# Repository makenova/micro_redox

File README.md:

# micro_redox

A family of 40% choc keyboards(34 keys) inspired by the Microdox and Ferris keyboards. 

 - The **micro_redox_split** is a pro-micro powered reversible split that does not require diodes.
 - The **micro_redox_semi_spit** is an integrated mcu semi split with usb-c and a rotary encoder.

Both boards can use either hot-swap sockets or the switches can be soldered directly to the pcb.

## Inspiration and differences

The Microdox(36 key MX spaced split) from Boardsource is a great keyboard. It was my first choc board, and after trying out a few keymaps, I realized I didn't need the outer thumb keys. In my experience, those keys are difficult to reach and do not serve a purpose on the keymap I've settled on.   
The Ferris(34 key choc spaced split) is another great keyboard. I like the look of the Ferris but a couple things made it uncomfortable for me to use:

* the thumb cluster is too close to the alphas 
* the pinky stagger is aggressive 

For the micro_redox family, I have kept the column stagger from the Microdox, made it choc spaced, and removed the outter thumb keys. I have also kept the distance between the homing keys and the thumb keys because I find it comfortable. Finally, I rotated the innermost thumb key which means that only 1u keycaps will fit there.  
For the split, I've also used a reversible pro-micro footprint so that both of them can face the same way i.e. component side down. It's a cleaner look.

## Libraries

These libraries that help me move fast. I may not actually be using them in this project, but adding them to keyboard projects is a habit. The are all added as git submodules so make sure you pull them down after you pull the repo.  
My thanks to the authors for sharing.

- [Keebio-components](https://github.com/keebio/keebio-components)
  - [@keebio](https://github.com/keebio)
- [Keebio-parts.pretty](https://github.com/keebio/Keebio-Parts.pretty)
  - [@keebio](https://github.com/keebio)
- [keyswtiches.pretty](https://github.com/daprice/keyswitches.pretty)
  - [@daprice](https://github.com/daprice)
- [random-keyboard-parts.pretty](https://github.com/ai03-2725/random-keyboard-parts.pretty)
  - [@ai03-2725](https://github.com/ai03-2725)
- [https://github.com/foostan/kbd](https://github.com/foostan/kbd)
  - [@foostan](https://github.com/foostan)
- [Customizable Rotary Encoder Knob](https://www.thingiverse.com/thing:2797118)
  - [tsw](https://www.thingiverse.com/tsw/designs)

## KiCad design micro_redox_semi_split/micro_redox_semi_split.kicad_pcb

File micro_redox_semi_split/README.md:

# micro_redox_semi_split

### Features

- USB C
- integrated mcu
- rotary encoder
- choc spaced
- hot-swap or soldered

There are production files in the "gerbers" directory for the pcb and a skeleton case.
Simply upload the zip files to your PCB manufacturer of choice.

If you do not get this assembled by a factory you can find an interactive BOM in `bom` directory.

Starting firmware can be found on my QMK fork in the [`makenova`](https://github.com/makenova/qmk_firmware/tree/makenova/keyboards/makenova//micro_redox/semi_split) branch.

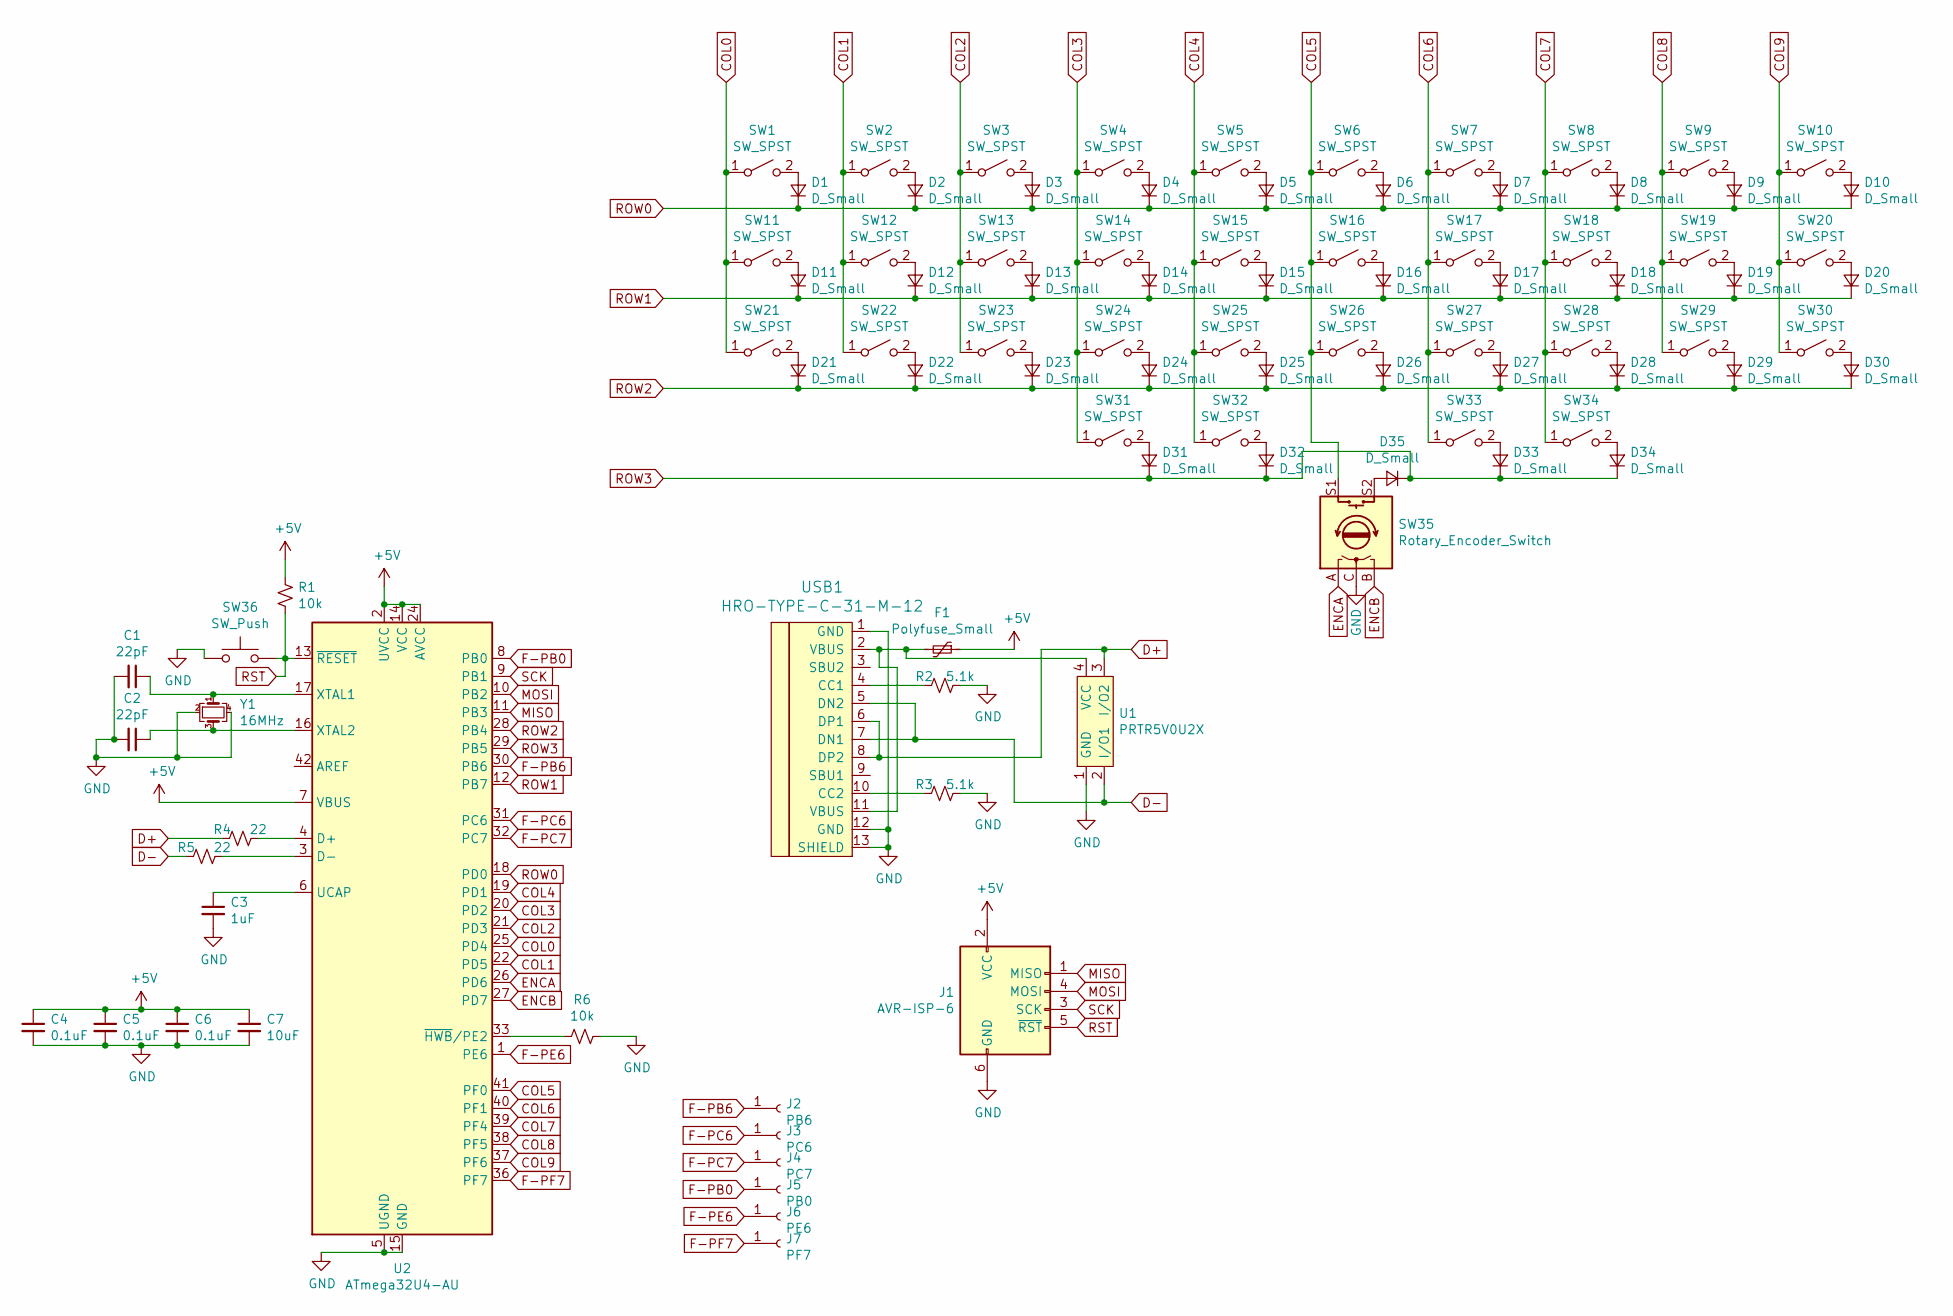
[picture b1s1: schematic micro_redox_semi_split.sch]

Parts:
C1, C2: 22pF; C_0805_2012Metric_Pad1.15x1.40mm_HandSolder
C3: 1uF; C_0805_2012Metric_Pad1.15x1.40mm_HandSolder
C4, C5, C6: 0.1uF; C_0805_2012Metric_Pad1.15x1.40mm_HandSolder
C7: 10uF; C_0805_2012Metric_Pad1.15x1.40mm_HandSolder
D1, D2, D3, D4, D5, D6, D7, D8, D9, D10, D11, D12, D13, D14, D15, D16, D17, D18, D19, D20, D21, D22, D23, D24, D25, D26, D27, D28, D29, D30, D31, D32, D33, D34, D35: D_Small; D_SOD-123
F1: Polyfuse_Small; Fuse_1206_3216Metric_Pad1.42x1.75mm_HandSolder
J1: AVR-ISP-6; ICSP-Header-ZigZag
J2: PB6; SinglePad
J3: PC6; SinglePad
J4: PC7; SinglePad
J5: PB0; SinglePad
J6: PE6; SinglePad
J7: PF7; SinglePad
R1, R6: 10k; R_0805_2012Metric_Pad1.15x1.40mm_HandSolder
R2, R3: 5.1k; R_0805_2012Metric_Pad1.15x1.40mm_HandSolder
R4, R5: 22; R_0805_2012Metric_Pad1.15x1.40mm_HandSolder
SW1, SW2, SW3, SW4, SW5, SW6, SW7, SW8, SW9, SW10, SW11, SW12, SW13, SW14, SW15, SW16, SW17, SW18, SW19, SW20, SW21, SW22, SW23, SW24, SW25, SW26, SW27, SW28, SW29, SW30, SW31, SW32, SW33, SW34: SW_SPST; Kailh_socket_PG1350_optional
SW35: Rotary_Encoder_Switch; RotaryEncoder_Alps_EC11E-Switch_Vertical_H20mm
SW36: SW_Push; SW_SPST_TL3342
U1: PRTR5V0U2X; SOT-143B
U2: ATmega32U4-AU; TQFP-44_10x10mm_P0.8mm
USB1: HRO-TYPE-C-31-M-12; HRO-TYPE-C-31-M-12-Assembly
Y1: 16MHz; Crystal_SMD_3225-4Pin_3.2x2.5mm_HandSoldering

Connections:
+5V: C4.1, C5.1, C6.1, C7.1, F1.1, J1.2 (VCC), R1.2, U2.2 (UVCC), U2.7 (VBUS), U2.14 (VCC), U2.24 (AVCC), U2.34 (VCC), U2.44 (AVCC)
COL0: SW1.1 (A), SW11.1 (A), SW21.1 (A), U2.25 (PD4)
COL1: SW2.1 (A), SW12.1 (A), SW22.1 (A), U2.22 (PD5)
COL2: SW3.1 (A), SW13.1 (A), SW23.1 (A), U2.21 (PD3)
COL3: SW4.1 (A), SW14.1 (A), SW24.1 (A), SW31.1 (A), U2.20 (PD2)
COL4: SW5.1 (A), SW15.1 (A), SW25.1 (A), SW32.1 (A), U2.19 (PD1)
COL5: SW6.1 (A), SW16.1 (A), SW26.1 (A), SW35.S1, U2.41 (PF0)
COL6: SW7.1 (A), SW17.1 (A), SW27.1 (A), SW33.1 (A), U2.40 (PF1)
COL7: SW8.1 (A), SW18.1 (A), SW28.1 (A), SW34.1 (A), U2.39 (PF4)
COL8: SW9.1 (A), SW19.1 (A), SW29.1 (A), U2.38 (PF5)
COL9: SW10.1 (A), SW20.1 (A), SW30.1 (A), U2.37 (PF6)
D+: R4.2, U1.3 (I/O2), USB1.6 (DP1), USB1.8 (DP2)
D-: R5.1, U1.2 (I/O1), USB1.5 (DN2), USB1.7 (DN1)
ENCA: SW35.A, U2.26 (PD6)
ENCB: SW35.B, U2.27 (PD7)
F-PB0: J5.1, U2.8 (PB0)
F-PB6: J2.1, U2.30 (PB6)
F-PC6: J3.1, U2.31 (PC6)
F-PC7: J4.1, U2.32 (PC7)
F-PE6: J6.1, U2.1 (PE6)
F-PF7: J7.1, U2.36 (PF7)
GND: C1.2, C2.2, C3.2, C4.2, C5.2, C6.2, C7.2, J1.6 (GND), R2.1, R3.1, R6.1, SW35.C, SW36.1, U1.1 (GND), U2.5 (UGND), U2.15 (GND), U2.23 (GND), U2.35 (GND), U2.43 (GND), USB1.1 (GND), USB1.12 (GND), USB1.13 (SHIELD), Y1.2, Y1.4
MISO: J1.1 (MISO), U2.11 (PB3)
MOSI: J1.4 (MOSI), U2.10 (PB2)
unnamed: C1.1, U2.17 (XTAL1), Y1.1
unnamed: C2.1, U2.16 (XTAL2), Y1.3
unnamed: C3.1, U2.6 (UCAP)
unnamed: D1.2 (A), SW1.2 (B)
unnamed: D2.2 (A), SW2.2 (B)
unnamed: D3.2 (A), SW3.2 (B)
unnamed: D4.2 (A), SW4.2 (B)
unnamed: D5.2 (A), SW5.2 (B)
unnamed: D6.2 (A), SW6.2 (B)
unnamed: D7.2 (A), SW7.2 (B)
unnamed: D8.2 (A), SW8.2 (B)
unnamed: D9.2 (A), SW9.2 (B)
unnamed: D10.2 (A), SW10.2 (B)
unnamed: D11.2 (A), SW11.2 (B)
unnamed: D12.2 (A), SW12.2 (B)
unnamed: D13.2 (A), SW13.2 (B)
unnamed: D14.2 (A), SW14.2 (B)
unnamed: D15.2 (A), SW15.2 (B)
unnamed: D16.2 (A), SW16.2 (B)
unnamed: D17.2 (A), SW17.2 (B)
unnamed: D18.2 (A), SW18.2 (B)
unnamed: D19.2 (A), SW19.2 (B)
unnamed: D20.2 (A), SW20.2 (B)
unnamed: D21.2 (A), SW21.2 (B)
unnamed: D22.2 (A), SW22.2 (B)
unnamed: D23.2 (A), SW23.2 (B)
unnamed: D24.2 (A), SW24.2 (B)
unnamed: D25.2 (A), SW25.2 (B)
unnamed: D26.2 (A), SW26.2 (B)
unnamed: D27.2 (A), SW27.2 (B)
unnamed: D28.2 (A), SW28.2 (B)
unnamed: D29.2 (A), SW29.2 (B)
unnamed: D30.2 (A), SW30.2 (B)
unnamed: D31.2 (A), SW31.2 (B)
unnamed: D32.2 (A), SW32.2 (B)
unnamed: D33.2 (A), SW33.2 (B)
unnamed: D34.2 (A), SW34.2 (B)
unnamed: D35.2 (A), SW35.S2
unnamed: F1.2, U1.4 (VCC), USB1.2 (VBUS), USB1.11 (VBUS)
unnamed: R2.2, USB1.4 (CC1)
unnamed: R3.2, USB1.10 (CC2)
unnamed: R4.1, U2.4 (D+)
unnamed: R5.2, U2.3 (D-)
unnamed: R6.2, U2.33 (~HWB~/PE2)
ROW0: D1.1 (K), D2.1 (K), D3.1 (K), D4.1 (K), D5.1 (K), D6.1 (K), D7.1 (K), D8.1 (K), D9.1 (K), D10.1 (K), U2.18 (PD0)
ROW1: D11.1 (K), D12.1 (K), D13.1 (K), D14.1 (K), D15.1 (K), D16.1 (K), D17.1 (K), D18.1 (K), D19.1 (K), D20.1 (K), U2.12 (PB7)
ROW2: D21.1 (K), D22.1 (K), D23.1 (K), D24.1 (K), D25.1 (K), D26.1 (K), D27.1 (K), D28.1 (K), D29.1 (K), D30.1 (K), U2.28 (PB4)
ROW3: D31.1 (K), D32.1 (K), D33.1 (K), D34.1 (K), D35.1 (K), U2.29 (PB5)
RST: J1.5 (~RST), R1.1, SW36.2, U2.13 (~RESET)
SCK: J1.3 (SCK), U2.9 (PB1)

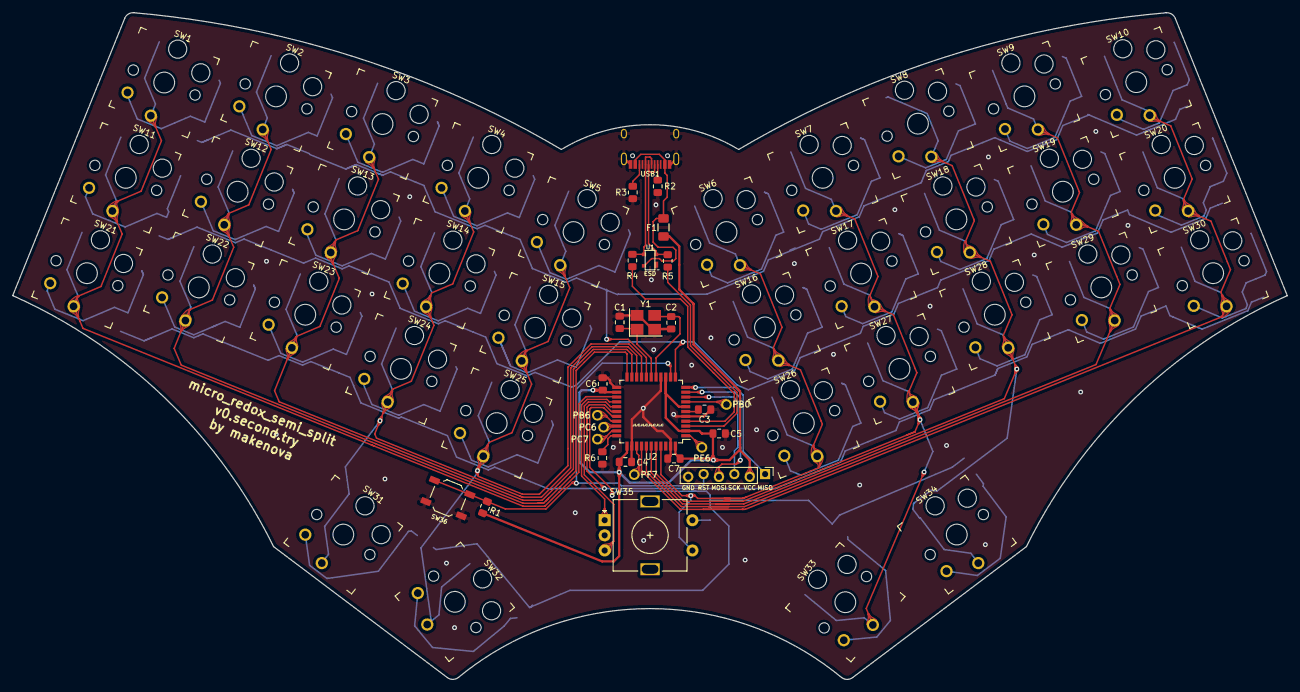
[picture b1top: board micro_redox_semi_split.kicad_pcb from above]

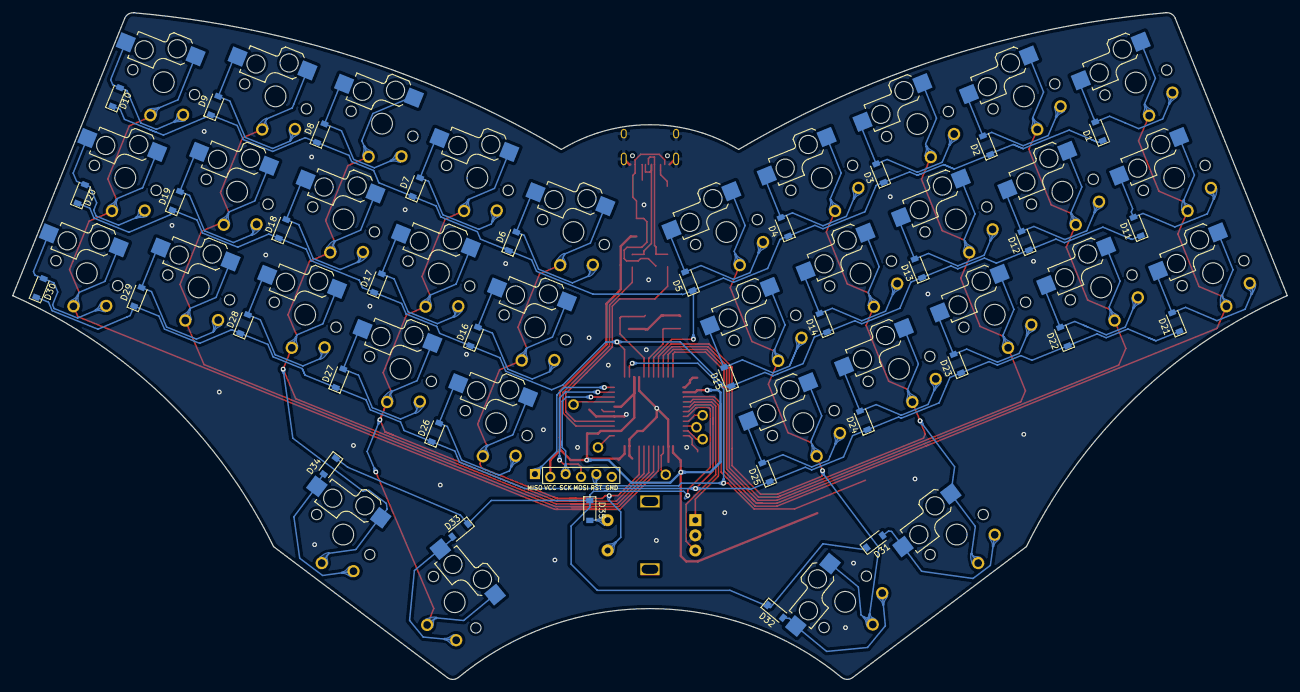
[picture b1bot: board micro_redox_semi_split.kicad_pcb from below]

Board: 2 copper layers, 210.6 x 110.1 mm, 96 parts (35 on the bottom side), 74 nets.

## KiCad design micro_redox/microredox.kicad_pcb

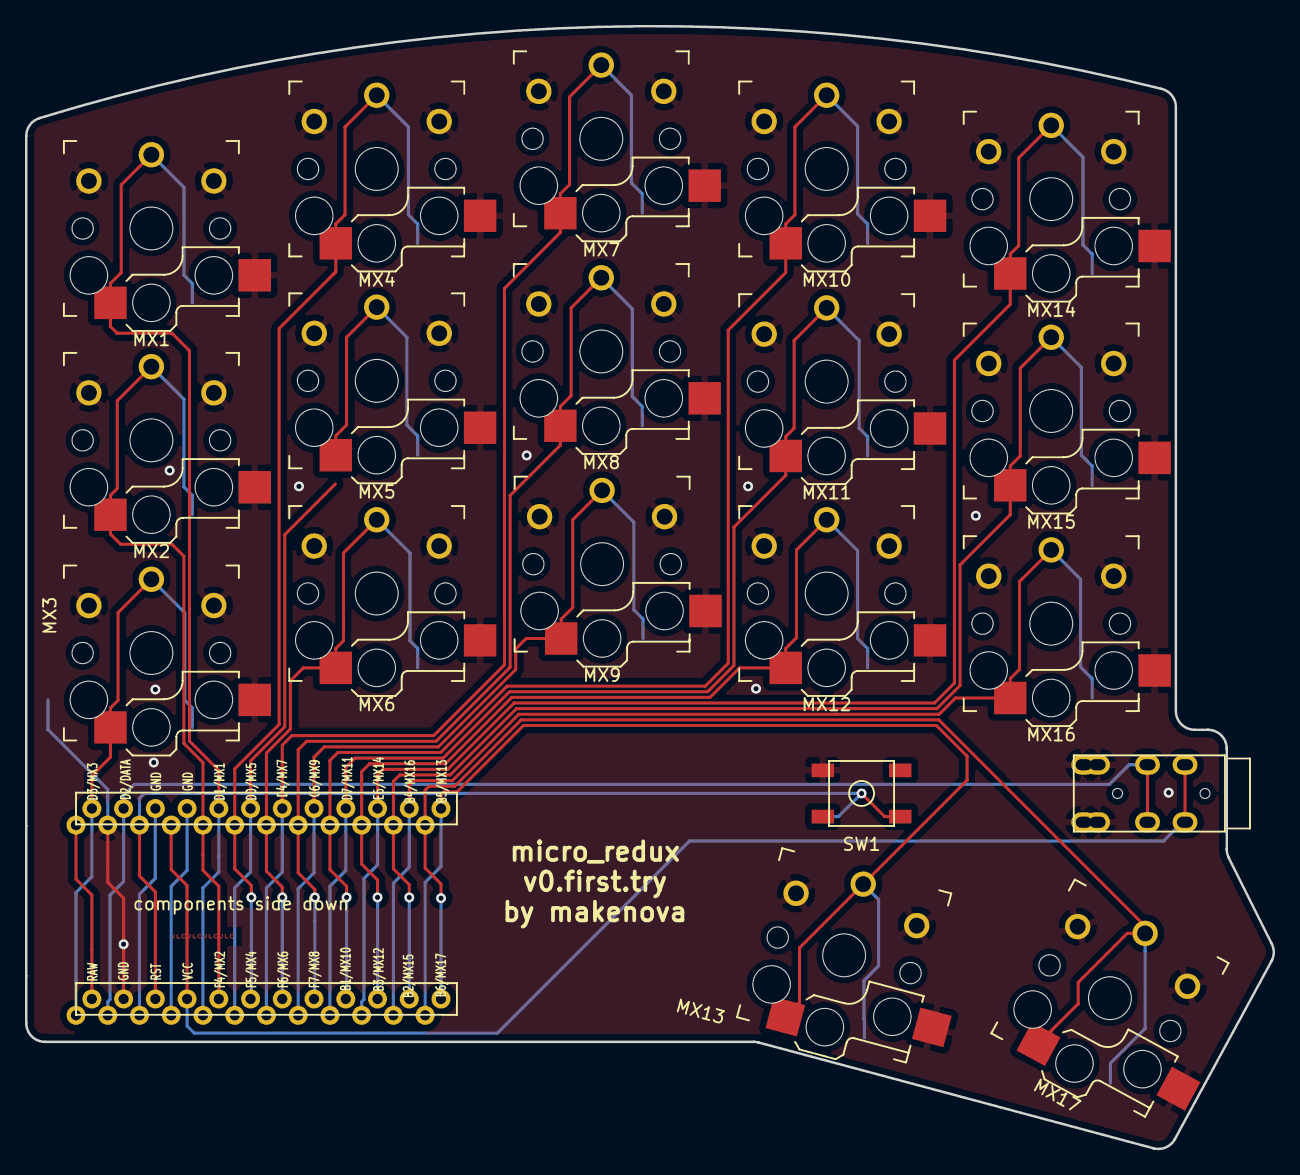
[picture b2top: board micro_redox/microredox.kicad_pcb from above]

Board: 2 copper layers, 99.8 x 89.8 mm, 20 parts (1 on the bottom side), 21 nets.

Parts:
MX1, MX2, MX3, MX4, MX5, MX6, MX7, MX8, MX9, MX10, MX11, MX12, MX13, MX14, MX15, MX16, MX17: MX-NoLED; Kailh_socket_PG1350_optional_reversible
SW1: SW_SPST; SKQG-1155865-makenova-reversible
U1: ProMicro; ProMicro_v2-makenova-micro-redox
U2: TRRS; TRRS-PJ-320A-no-Fmask-makenova-reversible

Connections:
+5V: U1.21, U2.4
DATA0: U1.2, U2.3
GND: MX1.2, MX2.2, MX3.2, MX4.2, MX5.2, MX6.2, MX7.2, MX8.2, MX9.2, MX10.2, MX11.2, MX12.2, MX13.2, MX14.2, MX15.2, MX16.2, MX17.2, SW1.2, U1.23, U2.1, U2.2
unnamed: SW1.1, U1.22
S1: MX1.1, U1.5
S2: MX2.1, U1.20
S3: MX3.1, U1.1
S4: MX4.1, U1.19
S5: MX5.1, U1.6
S6: MX6.1, U1.18
S7: MX7.1, U1.7
S8: MX8.1, U1.17
S9: MX9.1, U1.8
S10: MX10.1, U1.16
S11: MX11.1, U1.9
S12: MX12.1, U1.15
S13: MX13.1, U1.12
S14: MX14.1, U1.10
S15: MX15.1, U1.14
S16: MX16.1, U1.11
S17: MX17.1, U1.13

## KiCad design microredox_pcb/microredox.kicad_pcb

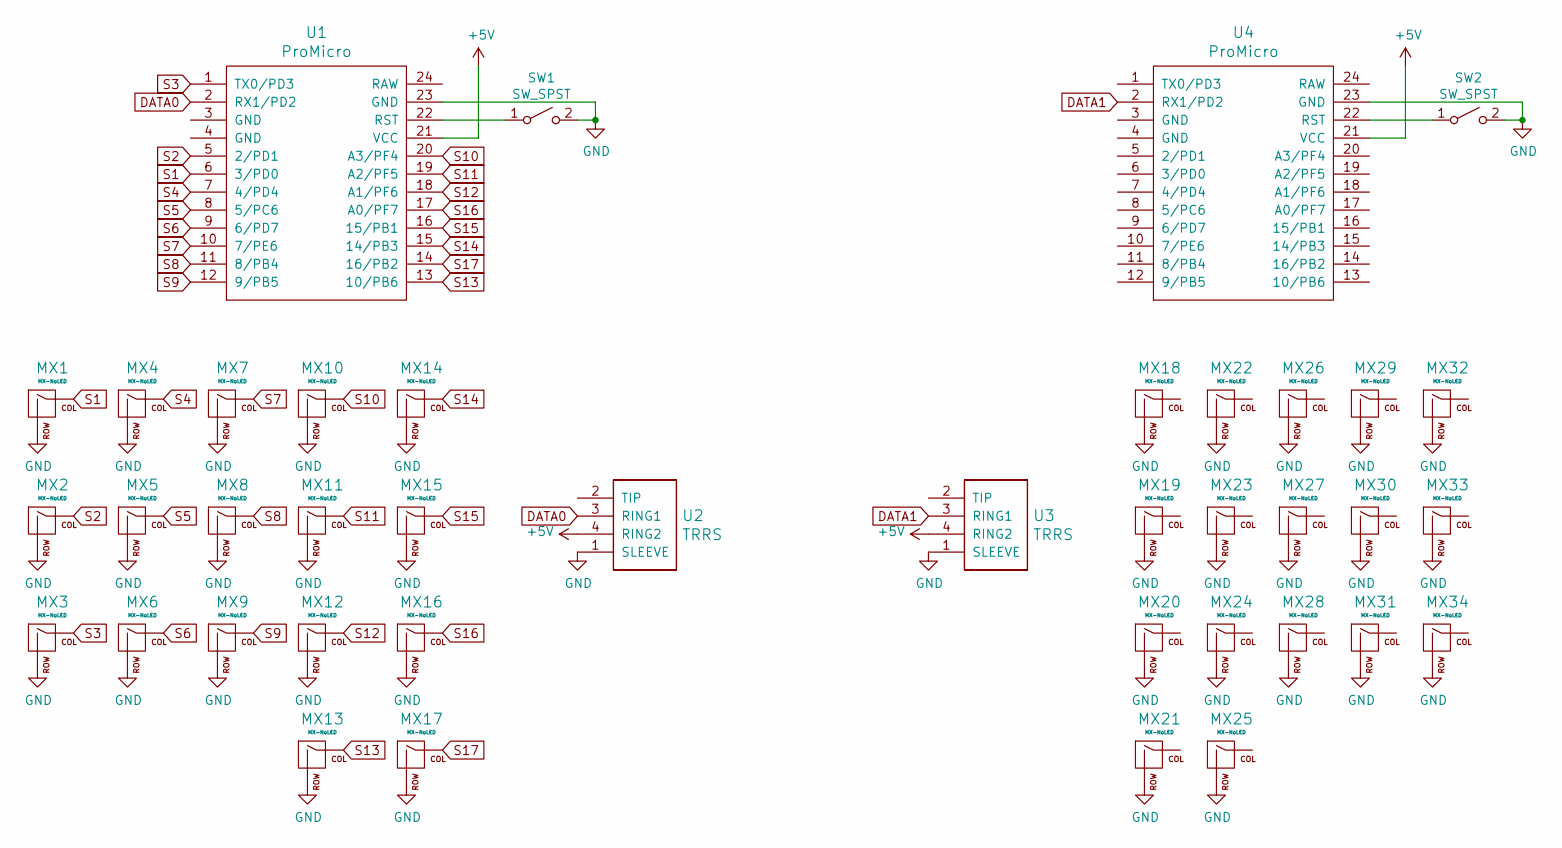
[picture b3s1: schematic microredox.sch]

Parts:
MX1, MX2, MX3, MX4, MX5, MX6, MX7, MX8, MX9, MX10, MX11, MX12, MX13, MX14, MX15, MX16, MX17, MX18, MX19, MX20, MX21, MX22, MX23, MX24, MX25, MX26, MX27, MX28, MX29, MX30, MX31, MX32, MX33, MX34: MX-NoLED; Kailh_socket_PG1350_optional
SW1, SW2: SW_SPST; SKQG-1155865
U1, U4: ProMicro; ArduinoProMicro-ZigZag
U2, U3: TRRS; TRRS-PJ-320A-no-Fmask

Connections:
+5V: U1.21 (VCC), U2.4 (RING2), U3.4 (RING2), U4.21 (VCC)
DATA0: U1.2 (RX1/PD2), U2.3 (RING1)
DATA1: U3.3 (RING1), U4.2 (RX1/PD2)
GND: MX1.2 (ROW), MX2.2 (ROW), MX3.2 (ROW), MX4.2 (ROW), MX5.2 (ROW), MX6.2 (ROW), MX7.2 (ROW), MX8.2 (ROW), MX9.2 (ROW), MX10.2 (ROW), MX11.2 (ROW), MX12.2 (ROW), MX13.2 (ROW), MX14.2 (ROW), MX15.2 (ROW), MX16.2 (ROW), MX17.2 (ROW), MX18.2 (ROW), MX19.2 (ROW), MX20.2 (ROW), MX21.2 (ROW), MX22.2 (ROW), MX23.2 (ROW), MX24.2 (ROW), MX25.2 (ROW), MX26.2 (ROW), MX27.2 (ROW), MX28.2 (ROW), MX29.2 (ROW), MX30.2 (ROW), MX31.2 (ROW), MX32.2 (ROW), MX33.2 (ROW), MX34.2 (ROW), SW1.2 (B), SW2.2 (B), U1.23 (GND), U2.1 (SLEEVE), U3.1 (SLEEVE), U4.23 (GND)
unnamed: SW1.1 (A), U1.22 (RST)
unnamed: SW2.1 (A), U4.22 (RST)
S1: MX1.1 (COL), U1.6 (3/PD0)
S2: MX2.1 (COL), U1.5 (2/PD1)
S3: MX3.1 (COL), U1.1 (TX0/PD3)
S4: MX4.1 (COL), U1.7 (4/PD4)
S5: MX5.1 (COL), U1.8 (5/PC6)
S6: MX6.1 (COL), U1.9 (6/PD7)
S7: MX7.1 (COL), U1.10 (7/PE6)
S8: MX8.1 (COL), U1.11 (8/PB4)
S9: MX9.1 (COL), U1.12 (9/PB5)
S10: MX10.1 (COL), U1.20 (A3/PF4)
S11: MX11.1 (COL), U1.19 (A2/PF5)
S12: MX12.1 (COL), U1.18 (A1/PF6)
S13: MX13.1 (COL), U1.13 (10/PB6)
S14: MX14.1 (COL), U1.15 (14/PB3)
S15: MX15.1 (COL), U1.16 (15/PB1)
S16: MX16.1 (COL), U1.17 (A0/PF7)
S17: MX17.1 (COL), U1.14 (16/PB2)

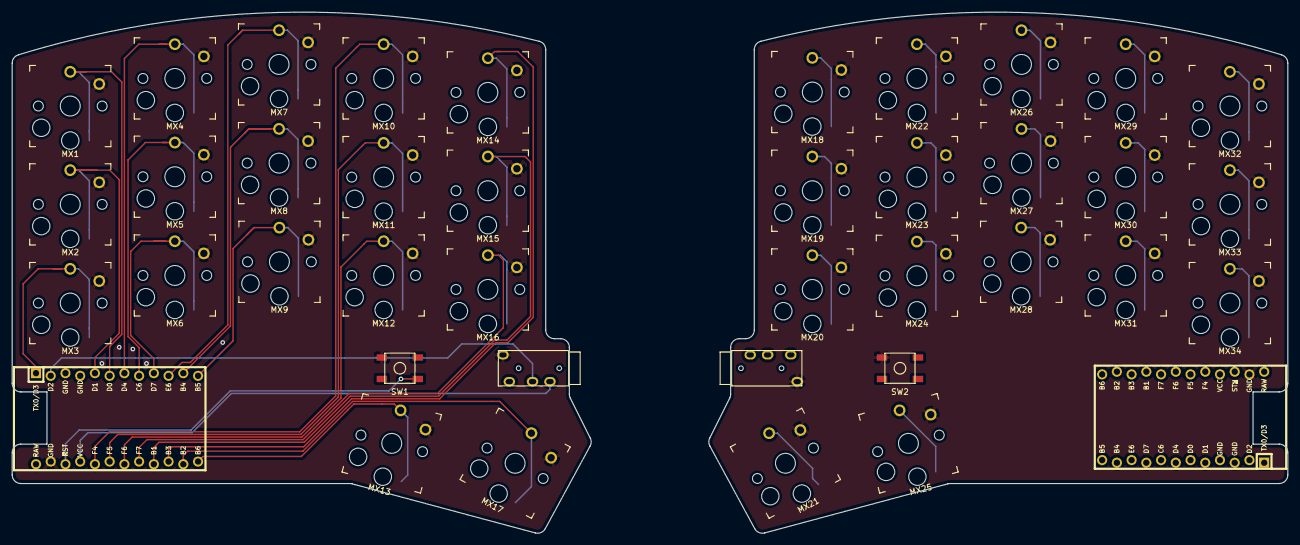
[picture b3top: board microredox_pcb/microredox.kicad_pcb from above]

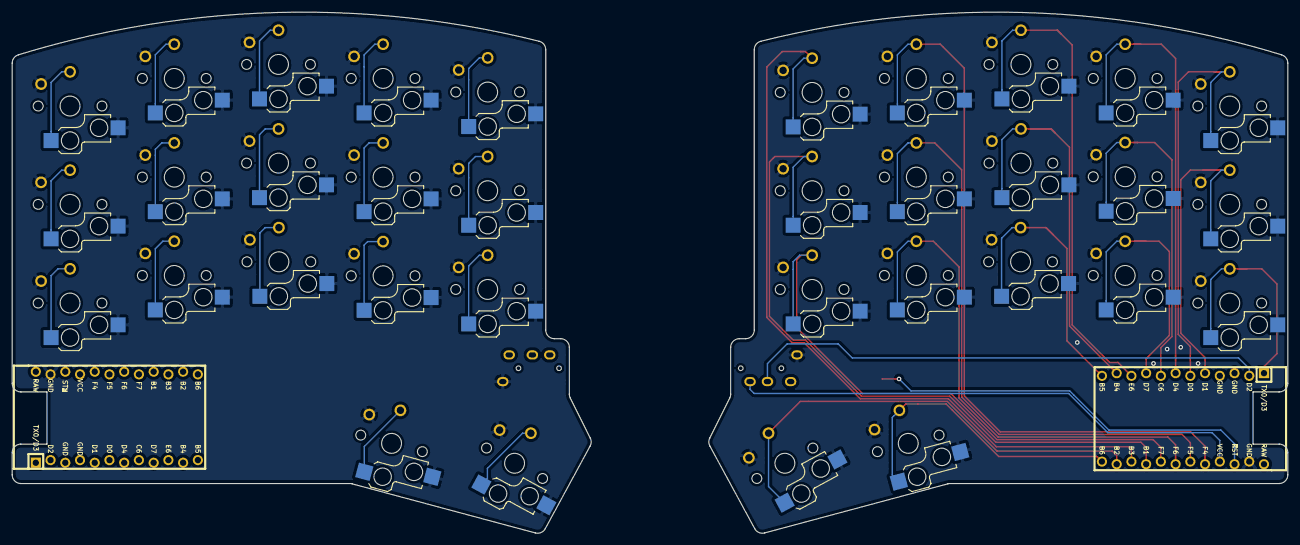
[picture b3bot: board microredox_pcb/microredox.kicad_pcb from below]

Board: 2 copper layers, 220.0 x 89.8 mm, 40 parts (2 on the bottom side), 23 nets.

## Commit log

2021-01-30 make it so
2021-02-04 add semi split
2021-02-07 touch up and try some plugins
2021-02-25 fixes for protos
2021-02-26 readme
2021-02-27 add slip-on case
2021-03-23 more stuff
